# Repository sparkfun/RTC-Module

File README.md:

SparkFun DS1307 RTC Module
==================

[  
*DS1307 Real Time Clock Module (BOB-12708)*](https://www.sparkfun.com/products/12708)

The Real Time Clock (RTC) module uses the DS1307 to keep track of the current year, month, day as well as the current time.

Repository Contents
-------------------
* **/Hardware** - All Eagle design files (.brd, .sch). These go way back in time (before github was around) so be sure to dig back to the original commit to see the early versions of the Eagle files.
* **/Production** - Various test jigs and large panel layouts used for production.

Documentation
--------------
* **[Installing an Arduino Library Guide](https://learn.sparkfun.com/tutorials/installing-an-arduino-library)** - Basic information on how to install an Arduino library.
* **[Library](https://github.com/sparkfun/SparkFun_DS1307_RTC_Arduino_Library)** - Arduino library for the SparkFun DS1307 RTC Module.
* **[Hookup Guide](https://learn.sparkfun.com/tutorials/real-time-clock-module-hookup-guide)** - Basic hookup guide for the SparkFun DS1307 RTC Module.

Version History
---------------
* [v1.3](https://www.sparkfun.com/products/retired/99) Version 1.3

License Information
-------------------

The hardware is released under [Creative Commons ShareAlike 4.0 International](https://creativecommons.org/licenses/by-sa/4.0/).
The code is beerware; if you see me (or any other SparkFun employee) at the local, and you've found our code helpful, please buy us a round!

Distributed as-is; no warranty is given.

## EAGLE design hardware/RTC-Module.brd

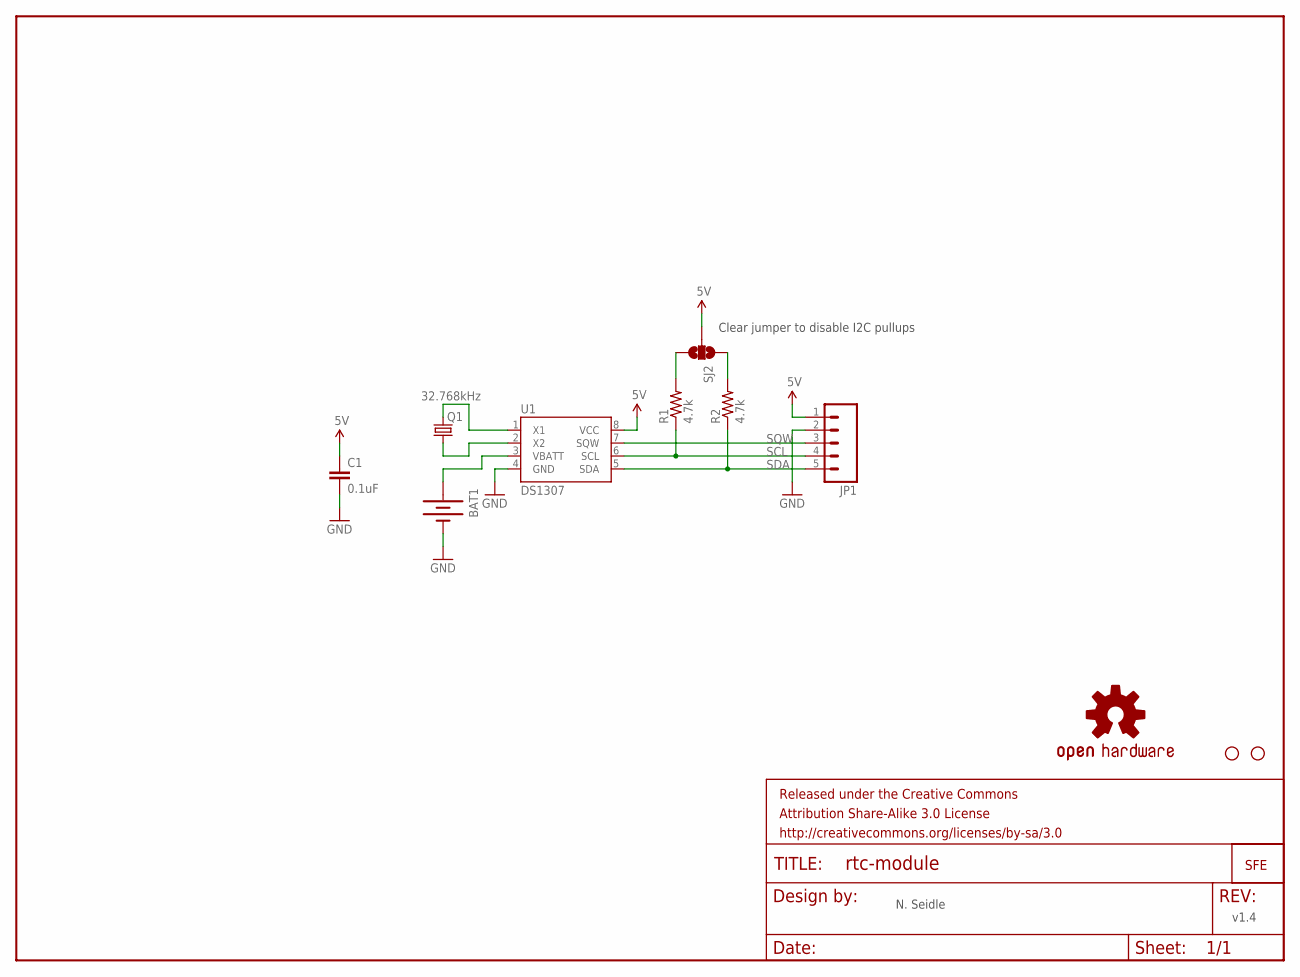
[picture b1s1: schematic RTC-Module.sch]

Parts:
BAT1: BATTERY12PTH; BATTCON_12MM_PTH
C1: 0.1uF; 0603-CAP
FRAME2: FRAME-LETTER; CREATIVE_COMMONS
JP1: M05PTH; 1X05
LOGO1: OSHW-LOGOS; OSHW-LOGO-S
Q1: 32.768kHz; CRYSTAL-32KHZ-SMD
R1, R2: 4.7k; 0603
SJ2: SOLDERJUMPER_2WAYPASTE1&2&3; SJ_3_PASTE1&2&3
U1: DS1307; SO08-TIGHT
U$1: LOGO-SFESK; SFE-LOGO-FLAME
U$6, U$7: STAND-OFF

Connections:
5V: C1.1, JP1.1, SJ2.2, U1.8 (VCC)
GND: BAT1.GND (-), C1.2, JP1.2, U1.4 (GND)
unnamed: Q1.X2 (2), U1.1 (X1)
unnamed: Q1.X1 (1), U1.2 (X2)
unnamed: BAT1.VCC@1 (+), U1.3 (VBATT)
unnamed: R1.2, SJ2.3
unnamed: R2.2, SJ2.1
SCL: JP1.4, R1.1, U1.6 (SCL)
SDA: JP1.5, R2.1, U1.5 (SDA)
SQW: JP1.3, U1.7 (SQW)

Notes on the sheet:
v1.4
N. Seidle
Clear jumper to disable I2C pullups

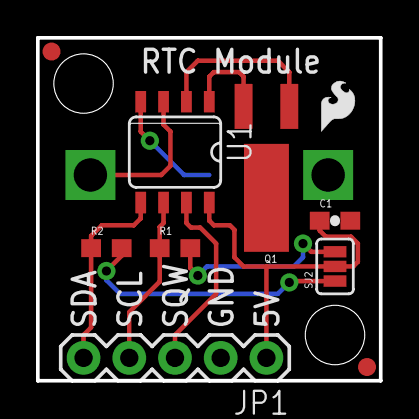
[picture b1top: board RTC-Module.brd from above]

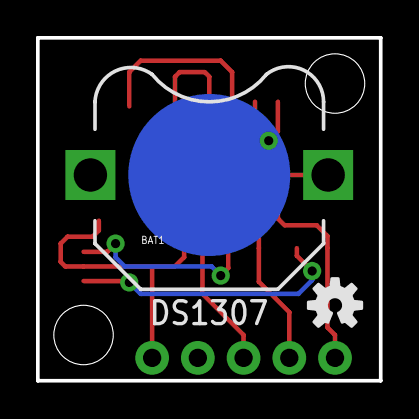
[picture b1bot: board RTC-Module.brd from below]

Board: 2 copper layers, 19.1 x 19.1 mm, 15 parts (2 on the bottom side), 10 nets.

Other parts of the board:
E$1, E$2: FIDUCIAL-1X2

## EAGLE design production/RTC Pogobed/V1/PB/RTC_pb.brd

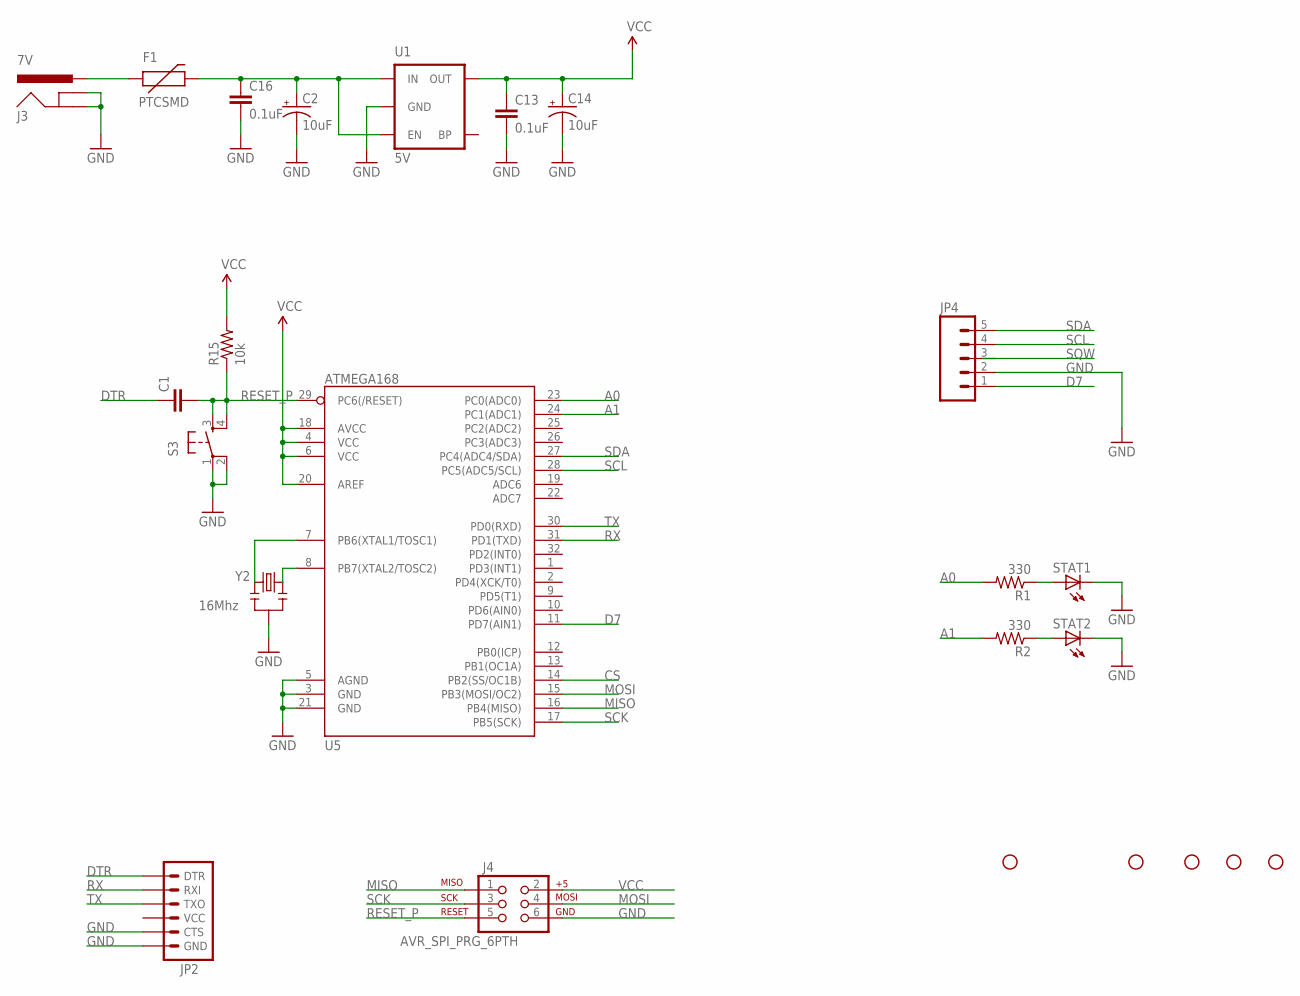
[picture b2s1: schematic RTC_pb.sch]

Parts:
C1: CAP0603-CAP; 0603-CAP
C2, C14: 10uF; EIA3216
C13, C16: 0.1uF; 0603-CAP
F1: PTCSMD; PTC-1206
J3: 7V; POWER_JACK_PTH_LOCK
J4: AVR_SPI_PRG_6PTH; 2X3
JP1, JP7, JP8, JP9, JP10: STAND-OFFTIGHT; STAND-OFF-TIGHT
JP2: ARDUINO_SERIAL_PROGRAMPTH; 1X06
JP4: M05PTH_LONGPADS; 1X05_LONGPADS
R1, R2: 330; 0603-RES
R15: 10k; 0603-RES
S3: TAC_SWITCHPTH; TACTILE-PTH
STAT1, STAT2: Yellow; LED-1206
U1: 3.3V; SOT23-5
U5: ATMEGA168; TQFP32-08
Y2: 8MHz; RESONATOR-SMD

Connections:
A0: R1.2, U5.23 (PC0(ADC0))
A1: R2.2, U5.24 (PC1(ADC1))
CS: U5.14 (PB2(SS/OC1B))
D7: JP4.1, U5.11 (PD7(AIN1))
DTR: C1.1, JP2.1 (DTR)
GND: C2.C (-), C13.2, C14.C (-), C16.2, J3.GND, J3.GNDBREAK, J4.6, JP2.5 (CTS), JP2.6 (GND), JP4.2, S3.1, S3.2, STAT1.C, STAT2.C, U1.2 (GND), U5.3 (GND), U5.5 (AGND), U5.21 (GND), Y2.2
MISO: J4.1, U5.16 (PB4(MISO))
MOSI: J4.4, U5.15 (PB3(MOSI/OC2))
unnamed: R1.1, STAT1.A
unnamed: R2.1, STAT2.A
unnamed: C2.A (+), C16.1, F1.2, U1.1 (IN), U1.3 (EN)
unnamed: U5.8 (PB7(XTAL2/TOSC2)), Y2.3
unnamed: U5.7 (PB6(XTAL1/TOSC1)), Y2.1
RAW: F1.1, J3.PWR
RESET_P: C1.2, J4.5, R15.1, S3.3, S3.4, U5.29 (PC6(/RESET))
RX: JP2.2 (RXI), U5.31 (PD1(TXD))
SCK: J4.3, U5.17 (PB5(SCK))
SCL: JP4.4, U5.28 (PC5(ADC5/SCL))
SDA: JP4.5, U5.27 (PC4(ADC4/SDA))
TX: JP2.3 (TXO), U5.30 (PD0(RXD))
VCC: C13.1, C14.A (+), J4.2, R15.2, U1.5 (OUT), U5.4 (VCC), U5.6 (VCC), U5.18 (AVCC), U5.20 (AREF)

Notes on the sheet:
16Mhz

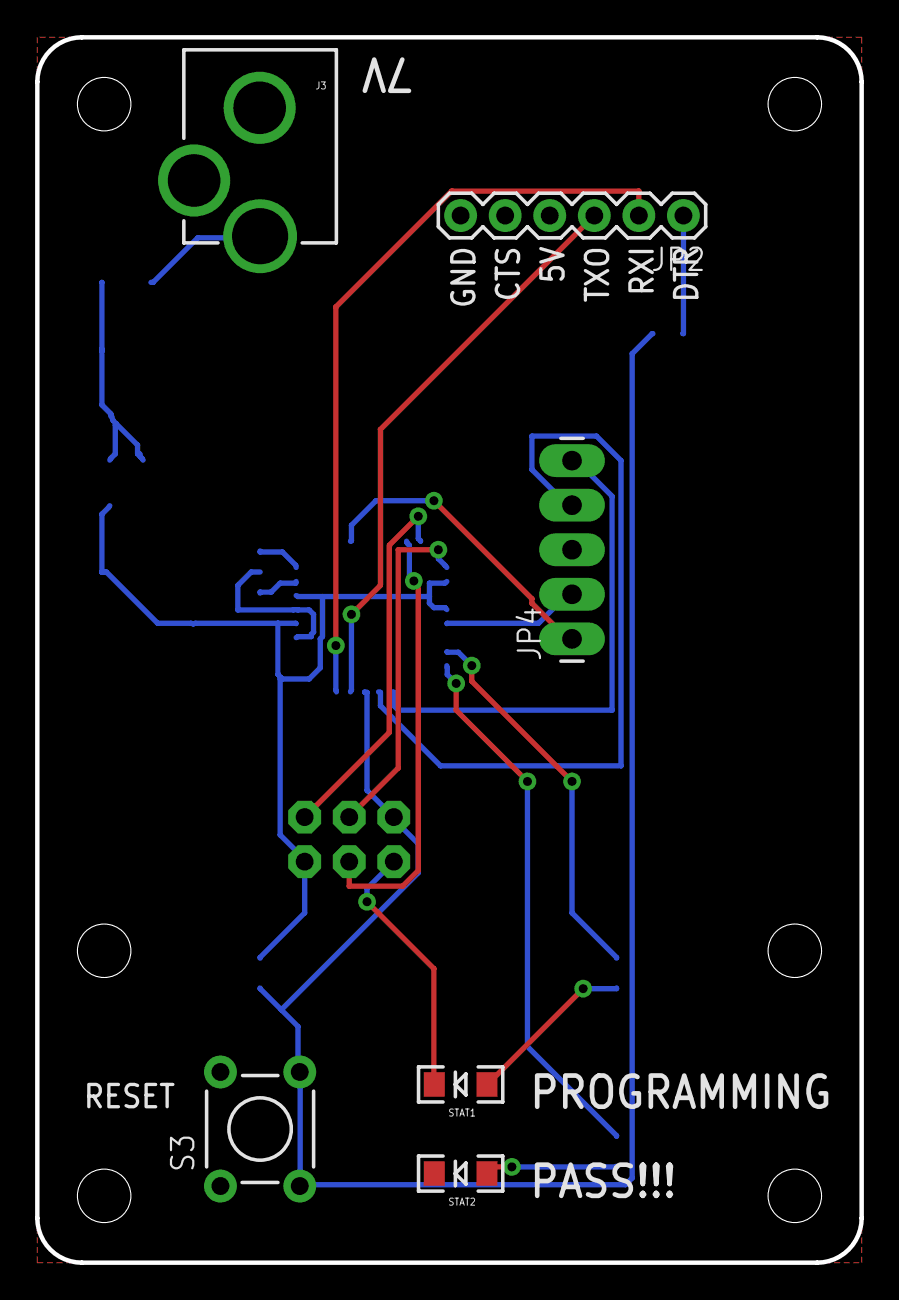
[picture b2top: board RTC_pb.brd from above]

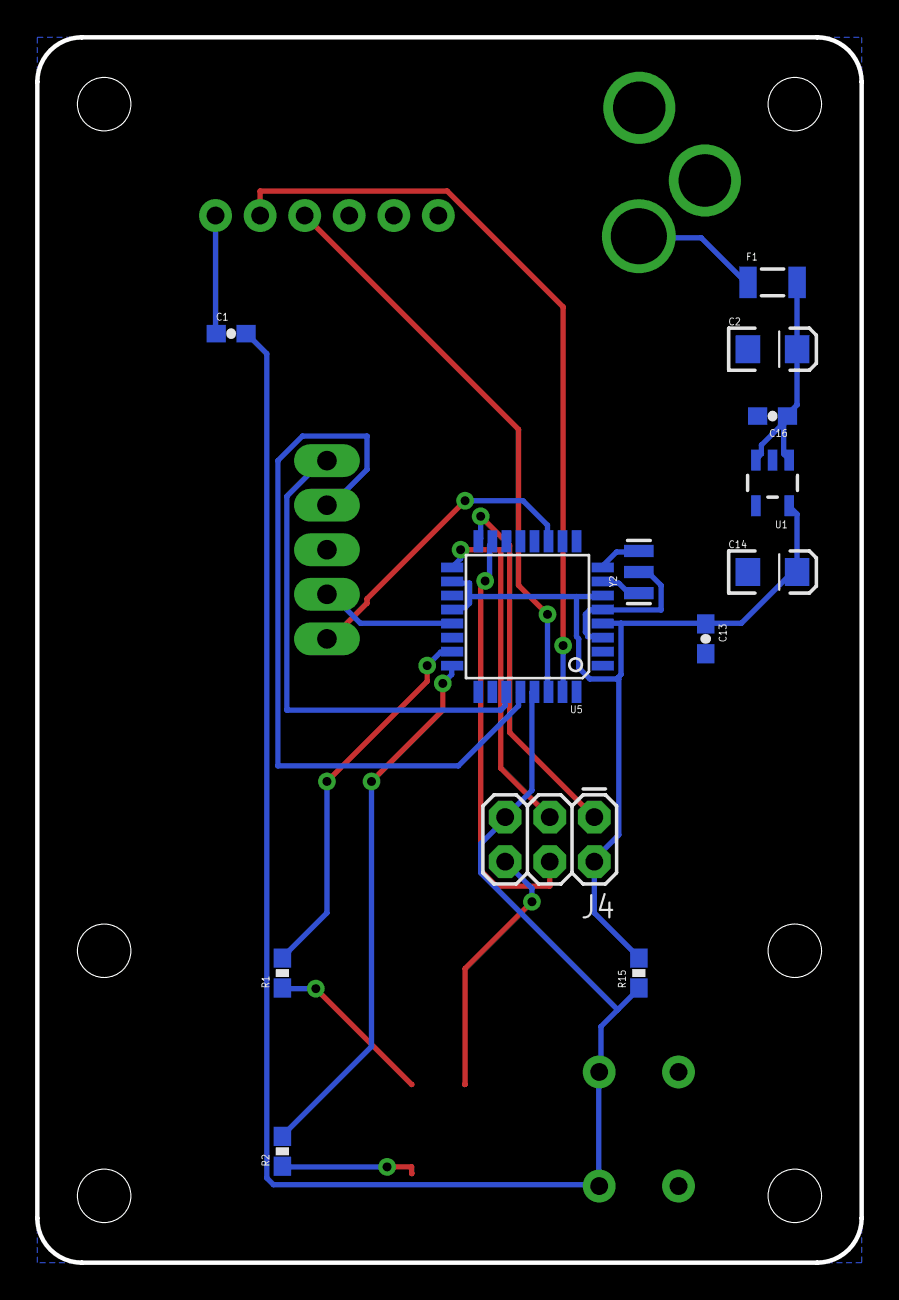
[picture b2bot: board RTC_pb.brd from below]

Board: 2 copper layers, 47.0 x 69.8 mm, 25 parts (13 on the bottom side), 20 nets.

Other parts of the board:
JP3: STAND-OFFTIGHT; STAND-OFF-TIGHT

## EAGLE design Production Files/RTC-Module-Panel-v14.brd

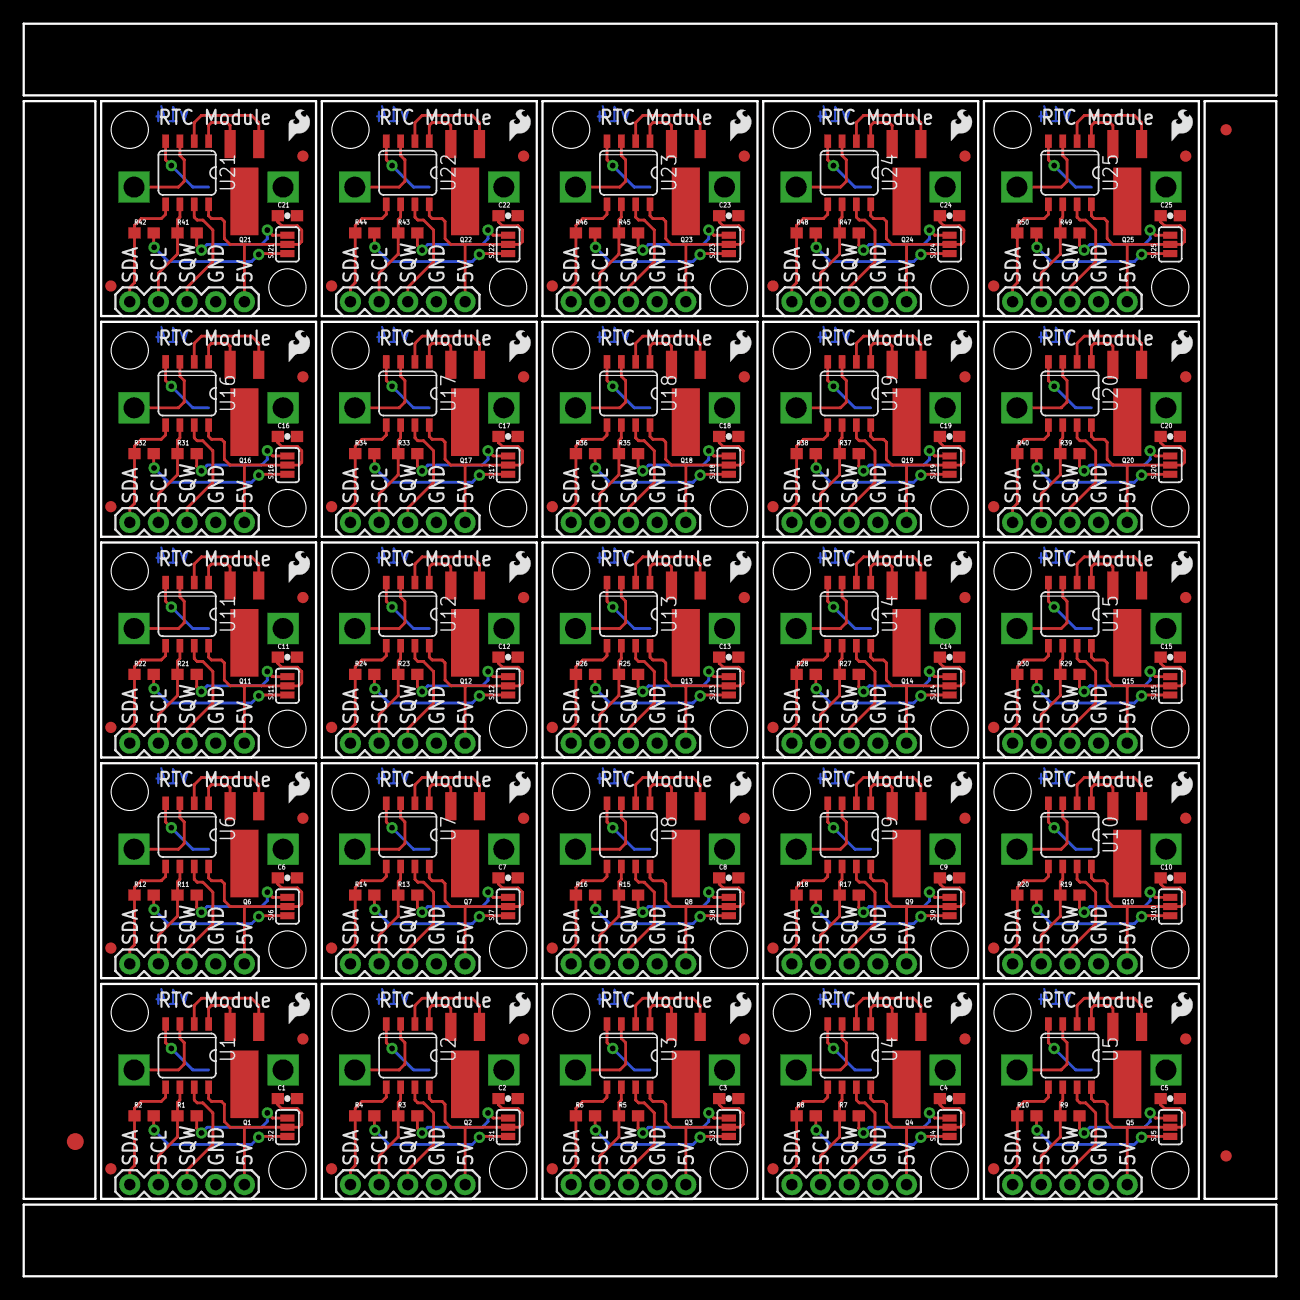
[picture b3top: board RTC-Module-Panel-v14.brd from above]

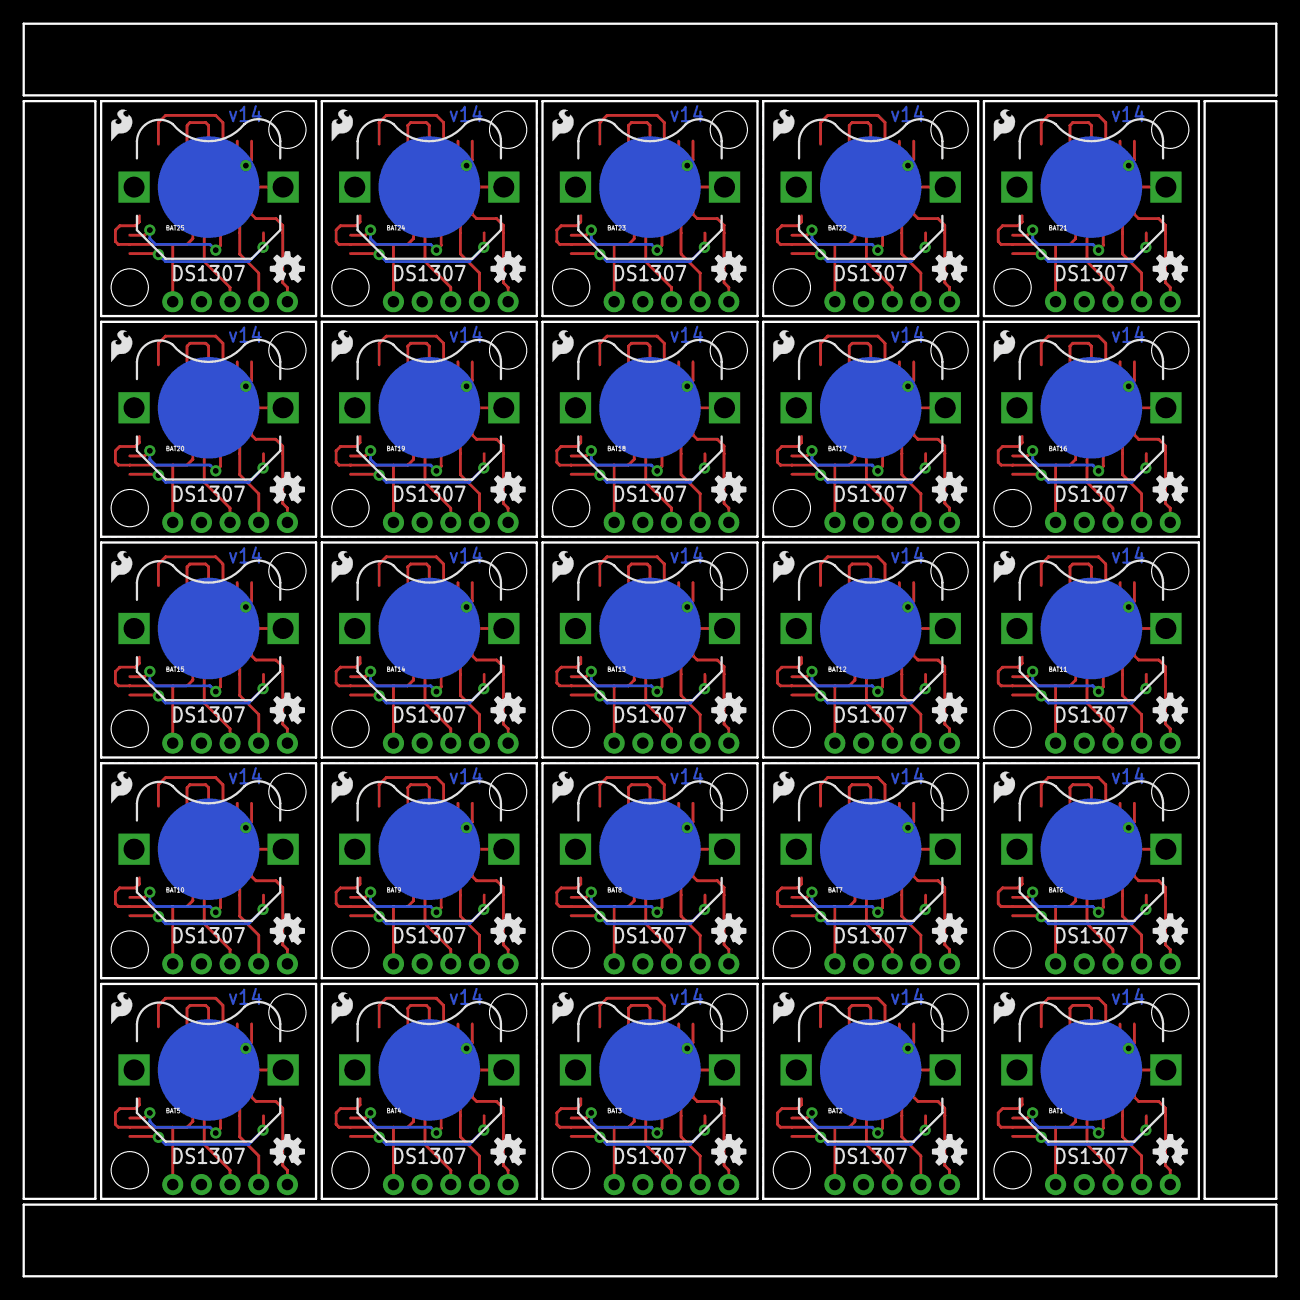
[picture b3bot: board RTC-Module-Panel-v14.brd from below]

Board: 2 copper layers, 111.0 x 111.0 mm, 378 parts (75 on the bottom side), 250 nets.

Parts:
BAT1, BAT2, BAT3, BAT4, BAT5, BAT6, BAT7, BAT8, BAT9, BAT10, BAT11, BAT12, BAT13, BAT14, BAT15, BAT16, BAT17, BAT18, BAT19, BAT20, BAT21, BAT22, BAT23, BAT24, BAT25: BATTCON_12MM_PTH
C1, C2, C3, C4, C5, C6, C7, C8, C9, C10, C11, C12, C13, C14, C15, C16, C17, C18, C19, C20, C21, C22, C23, C24, C25: 0.1uF; 0603-CAP
E$1, E$2, E$3, E$4, E$5, E$6, E$7, E$8, E$9, E$10, E$11, E$12, E$13, E$14, E$15, E$16, E$17, E$18, E$19, E$20, E$21, E$22, E$23, E$24, E$25, E$26, E$27, E$28, E$29, E$30, E$31, E$32, E$33, E$34, E$35, E$36, E$37, E$38, E$39, E$40, E$41, E$42, E$43, E$44, E$45, E$46, E$47, E$48, E$49, E$50, E$54, E$55: FIDUCIAL-1X2
E$51: FIDUCIAL-1.5X3
JP1, JP2, JP3, JP4, JP5, JP6, JP7, JP8, JP9, JP10, JP11, JP12, JP13, JP14, JP15, JP16, JP17, JP18, JP19, JP20, JP21, JP22, JP23, JP24, JP25: 1X05
LOGO1, LOGO2, LOGO3, LOGO4, LOGO5, LOGO6, LOGO7, LOGO8, LOGO9, LOGO10, LOGO11, LOGO12, LOGO13, LOGO14, LOGO15, LOGO16, LOGO17, LOGO18, LOGO19, LOGO20, LOGO21, LOGO22, LOGO23, LOGO24, LOGO25: OSHW-LOGOS; OSHW-LOGO-S
Q1, Q2, Q3, Q4, Q5, Q6, Q7, Q8, Q9, Q10, Q11, Q12, Q13, Q14, Q15, Q16, Q17, Q18, Q19, Q20, Q21, Q22, Q23, Q24, Q25: 32.768kHz; CRYSTAL-32KHZ-SMD
R1, R2, R3, R4, R5, R6, R7, R8, R9, R10, R11, R12, R13, R14, R15, R16, R17, R18, R19, R20, R21, R22, R23, R24, R25, R26, R27, R28, R29, R30, R31, R32, R33, R34, R35, R36, R37, R38, R39, R40, R41, R42, R43, R44, R45, R46, R47, R48, R49, R50: 4.7k; 0603
SJ1, SJ2, SJ3, SJ4, SJ5, SJ6, SJ7, SJ8, SJ9, SJ10, SJ11, SJ12, SJ13, SJ14, SJ15, SJ16, SJ17, SJ18, SJ19, SJ20, SJ21, SJ22, SJ23, SJ24, SJ25: SJ_3_PASTE1&2&3
U1, U2, U3, U4, U5, U6, U7, U8, U9, U10, U11, U12, U13, U14, U15, U16, U17, U18, U19, U20, U21, U22, U23, U24, U25: DS1307; SO08-TIGHT
U$1, U$2, U$3, U$8, U$9, U$12, U$13, U$16, U$17, U$20, U$21, U$24, U$25, U$28, U$29, U$32, U$33, U$36, U$37, U$40, U$41, U$44, U$45, U$48, U$49, U$52, U$53, U$56, U$57, U$60, U$61, U$64, U$65, U$68, U$69, U$72, U$73, U$76, U$77, U$80, U$81, U$84, U$85, U$88, U$89, U$92, U$93, U$96, U$97, U$100: LOGO-SFESK; SFE-LOGO-FLAME
U$4, U$5, U$6, U$7, U$10, U$11, U$14, U$15, U$18, U$19, U$22, U$23, U$26, U$27, U$30, U$31, U$34, U$35, U$38, U$39, U$42, U$43, U$46, U$47, U$50, U$51, U$54, U$55, U$58, U$59, U$62, U$63, U$66, U$67, U$70, U$71, U$74, U$75, U$78, U$79, U$82, U$83, U$86, U$87, U$90, U$91, U$94, U$95, U$98, U$99: STAND-OFF

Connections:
5V: C1.1, JP1.1, SJ2.2, U1.8
5V1: C2.1, JP2.1, SJ1.2, U2.8
5V2: C3.1, JP3.1, SJ3.2, U3.8
5V3: C4.1, JP4.1, SJ4.2, U4.8
5V4: C5.1, JP5.1, SJ5.2, U5.8
5V5: C6.1, JP6.1, SJ6.2, U6.8
5V6: C7.1, JP7.1, SJ7.2, U7.8
5V7: C8.1, JP8.1, SJ8.2, U8.8
5V8: C9.1, JP9.1, SJ9.2, U9.8
5V9: C10.1, JP10.1, SJ10.2, U10.8
5V10: C11.1, JP11.1, SJ11.2, U11.8
5V11: C12.1, JP12.1, SJ12.2, U12.8
5V12: C13.1, JP13.1, SJ13.2, U13.8
5V13: C14.1, JP14.1, SJ14.2, U14.8
5V14: C15.1, JP15.1, SJ15.2, U15.8
5V15: C16.1, JP16.1, SJ16.2, U16.8
5V16: C17.1, JP17.1, SJ17.2, U17.8
5V17: C18.1, JP18.1, SJ18.2, U18.8
5V18: C19.1, JP19.1, SJ19.2, U19.8
5V19: C20.1, JP20.1, SJ20.2, U20.8
5V20: C21.1, JP21.1, SJ21.2, U21.8
5V21: C22.1, JP22.1, SJ22.2, U22.8
5V22: C23.1, JP23.1, SJ23.2, U23.8
5V23: C24.1, JP24.1, SJ24.2, U24.8
5V24: C25.1, JP25.1, SJ25.2, U25.8
GND: BAT1.GND, C1.2, JP1.2, U1.4
GND1: BAT2.GND, C2.2, JP2.2, U2.4
GND2: BAT3.GND, C3.2, JP3.2, U3.4
GND3: BAT4.GND, C4.2, JP4.2, U4.4
GND4: BAT5.GND, C5.2, JP5.2, U5.4
GND5: BAT6.GND, C6.2, JP6.2, U6.4
GND6: BAT7.GND, C7.2, JP7.2, U7.4
GND7: BAT8.GND, C8.2, JP8.2, U8.4
GND8: BAT9.GND, C9.2, JP9.2, U9.4
GND9: BAT10.GND, C10.2, JP10.2, U10.4
GND10: BAT11.GND, C11.2, JP11.2, U11.4
GND11: BAT12.GND, C12.2, JP12.2, U12.4
GND12: BAT13.GND, C13.2, JP13.2, U13.4
GND13: BAT14.GND, C14.2, JP14.2, U14.4
GND14: BAT15.GND, C15.2, JP15.2, U15.4
GND15: BAT16.GND, C16.2, JP16.2, U16.4
GND16: BAT17.GND, C17.2, JP17.2, U17.4
GND17: BAT18.GND, C18.2, JP18.2, U18.4
GND18: BAT19.GND, C19.2, JP19.2, U19.4
GND19: BAT20.GND, C20.2, JP20.2, U20.4
GND20: BAT21.GND, C21.2, JP21.2, U21.4
GND21: BAT22.GND, C22.2, JP22.2, U22.4
GND22: BAT23.GND, C23.2, JP23.2, U23.4
GND23: BAT24.GND, C24.2, JP24.2, U24.4
GND24: BAT25.GND, C25.2, JP25.2, U25.4
unnamed: Q1.X2, U1.1
unnamed: Q1.X1, U1.2
unnamed: Q2.X2, U2.1
unnamed: BAT1.VCC@1, U1.3
unnamed: R1.2, SJ2.3
unnamed: R2.2, SJ2.1
unnamed: Q2.X1, U2.2
unnamed: BAT2.VCC@1, U2.3
unnamed: R3.2, SJ1.3
unnamed: R4.2, SJ1.1
unnamed: Q3.X2, U3.1
unnamed: Q3.X1, U3.2
unnamed: BAT3.VCC@1, U3.3
unnamed: R5.2, SJ3.3
unnamed: R6.2, SJ3.1
unnamed: Q4.X2, U4.1
unnamed: Q4.X1, U4.2
unnamed: BAT4.VCC@1, U4.3
unnamed: R7.2, SJ4.3
unnamed: R8.2, SJ4.1
unnamed: Q5.X2, U5.1
unnamed: Q5.X1, U5.2
unnamed: BAT5.VCC@1, U5.3
unnamed: R9.2, SJ5.3
unnamed: R10.2, SJ5.1
unnamed: Q6.X2, U6.1
unnamed: Q6.X1, U6.2
unnamed: BAT6.VCC@1, U6.3
unnamed: R11.2, SJ6.3
unnamed: R12.2, SJ6.1
unnamed: Q7.X2, U7.1
unnamed: Q7.X1, U7.2
unnamed: BAT7.VCC@1, U7.3
unnamed: R13.2, SJ7.3
unnamed: R14.2, SJ7.1
unnamed: Q8.X2, U8.1
unnamed: Q8.X1, U8.2
unnamed: BAT8.VCC@1, U8.3
unnamed: R15.2, SJ8.3
unnamed: R16.2, SJ8.1
unnamed: Q9.X2, U9.1
unnamed: Q9.X1, U9.2
unnamed: BAT9.VCC@1, U9.3
unnamed: R17.2, SJ9.3
unnamed: R18.2, SJ9.1
unnamed: Q10.X2, U10.1
unnamed: Q10.X1, U10.2
unnamed: BAT10.VCC@1, U10.3
unnamed: R19.2, SJ10.3
unnamed: R20.2, SJ10.1
unnamed: Q11.X2, U11.1
unnamed: Q11.X1, U11.2
unnamed: BAT11.VCC@1, U11.3
unnamed: R21.2, SJ11.3
unnamed: R22.2, SJ11.1
unnamed: Q12.X2, U12.1
unnamed: Q12.X1, U12.2
unnamed: BAT12.VCC@1, U12.3
unnamed: R23.2, SJ12.3
unnamed: R24.2, SJ12.1
unnamed: Q13.X2, U13.1
unnamed: Q13.X1, U13.2
unnamed: BAT13.VCC@1, U13.3
unnamed: R25.2, SJ13.3
unnamed: R26.2, SJ13.1
unnamed: Q14.X2, U14.1
unnamed: Q14.X1, U14.2
unnamed: BAT14.VCC@1, U14.3
unnamed: R27.2, SJ14.3
unnamed: R28.2, SJ14.1
unnamed: Q15.X2, U15.1
unnamed: Q15.X1, U15.2
unnamed: BAT15.VCC@1, U15.3
unnamed: R29.2, SJ15.3
unnamed: R30.2, SJ15.1
unnamed: Q16.X2, U16.1
unnamed: Q16.X1, U16.2
unnamed: BAT16.VCC@1, U16.3
unnamed: R31.2, SJ16.3
unnamed: R32.2, SJ16.1
unnamed: Q17.X2, U17.1
unnamed: Q17.X1, U17.2
unnamed: BAT17.VCC@1, U17.3
unnamed: R33.2, SJ17.3
unnamed: R34.2, SJ17.1
unnamed: Q18.X2, U18.1
unnamed: Q18.X1, U18.2
unnamed: BAT18.VCC@1, U18.3
unnamed: R35.2, SJ18.3
unnamed: R36.2, SJ18.1
unnamed: Q19.X2, U19.1
unnamed: Q19.X1, U19.2
unnamed: BAT19.VCC@1, U19.3
unnamed: R37.2, SJ19.3
unnamed: R38.2, SJ19.1
unnamed: Q20.X2, U20.1
unnamed: Q20.X1, U20.2
unnamed: BAT20.VCC@1, U20.3
unnamed: R39.2, SJ20.3
unnamed: R40.2, SJ20.1
unnamed: Q21.X2, U21.1
unnamed: Q21.X1, U21.2
unnamed: BAT21.VCC@1, U21.3
unnamed: R41.2, SJ21.3
unnamed: R42.2, SJ21.1
unnamed: Q22.X2, U22.1
unnamed: Q22.X1, U22.2
unnamed: BAT22.VCC@1, U22.3
unnamed: R43.2, SJ22.3
unnamed: R44.2, SJ22.1
unnamed: Q23.X2, U23.1
unnamed: Q23.X1, U23.2
unnamed: BAT23.VCC@1, U23.3
unnamed: R45.2, SJ23.3
unnamed: R46.2, SJ23.1
unnamed: Q24.X2, U24.1
unnamed: Q24.X1, U24.2
unnamed: BAT24.VCC@1, U24.3
unnamed: R47.2, SJ24.3
unnamed: R48.2, SJ24.1
unnamed: Q25.X2, U25.1
unnamed: Q25.X1, U25.2
unnamed: BAT25.VCC@1, U25.3
unnamed: R49.2, SJ25.3
unnamed: R50.2, SJ25.1
SCL: JP1.4, R1.1, U1.6
SCL1: JP2.4, R3.1, U2.6
SCL2: JP3.4, R5.1, U3.6
SCL3: JP4.4, R7.1, U4.6
SCL4: JP5.4, R9.1, U5.6
SCL5: JP6.4, R11.1, U6.6
SCL6: JP7.4, R13.1, U7.6
SCL7: JP8.4, R15.1, U8.6
SCL8: JP9.4, R17.1, U9.6
SCL9: JP10.4, R19.1, U10.6
SCL10: JP11.4, R21.1, U11.6
SCL11: JP12.4, R23.1, U12.6
SCL12: JP13.4, R25.1, U13.6
SCL13: JP14.4, R27.1, U14.6
SCL14: JP15.4, R29.1, U15.6
SCL15: JP16.4, R31.1, U16.6
SCL16: JP17.4, R33.1, U17.6
SCL17: JP18.4, R35.1, U18.6
SCL18: JP19.4, R37.1, U19.6
SCL19: JP20.4, R39.1, U20.6
SCL20: JP21.4, R41.1, U21.6
SCL21: JP22.4, R43.1, U22.6
SCL22: JP23.4, R45.1, U23.6
SCL23: JP24.4, R47.1, U24.6
SCL24: JP25.4, R49.1, U25.6
SDA: JP1.5, R2.1, U1.5
SDA1: JP2.5, R4.1, U2.5
SDA2: JP3.5, R6.1, U3.5
SDA3: JP4.5, R8.1, U4.5
SDA4: JP5.5, R10.1, U5.5
SDA5: JP6.5, R12.1, U6.5
SDA6: JP7.5, R14.1, U7.5
SDA7: JP8.5, R16.1, U8.5
SDA8: JP9.5, R18.1, U9.5
SDA9: JP10.5, R20.1, U10.5
SDA10: JP11.5, R22.1, U11.5
SDA11: JP12.5, R24.1, U12.5
SDA12: JP13.5, R26.1, U13.5
SDA13: JP14.5, R28.1, U14.5
SDA14: JP15.5, R30.1, U15.5
SDA15: JP16.5, R32.1, U16.5
SDA16: JP17.5, R34.1, U17.5
SDA17: JP18.5, R36.1, U18.5
SDA18: JP19.5, R38.1, U19.5
SDA19: JP20.5, R40.1, U20.5
SDA20: JP21.5, R42.1, U21.5
SDA21: JP22.5, R44.1, U22.5
SDA22: JP23.5, R46.1, U23.5
SDA23: JP24.5, R48.1, U24.5
SDA24: JP25.5, R50.1, U25.5
SQW: JP1.3, U1.7
SQW1: JP2.3, U2.7
SQW2: JP3.3, U3.7
SQW3: JP4.3, U4.7
SQW4: JP5.3, U5.7
SQW5: JP6.3, U6.7
SQW6: JP7.3, U7.7
SQW7: JP8.3, U8.7
SQW8: JP9.3, U9.7
SQW9: JP10.3, U10.7
SQW10: JP11.3, U11.7
SQW11: JP12.3, U12.7
SQW12: JP13.3, U13.7
SQW13: JP14.3, U14.7
SQW14: JP15.3, U15.7
SQW15: JP16.3, U16.7
SQW16: JP17.3, U17.7
SQW17: JP18.3, U18.7
SQW18: JP19.3, U19.7
SQW19: JP20.3, U20.7
SQW20: JP21.3, U21.7
SQW21: JP22.3, U22.7
SQW22: JP23.3, U23.7
SQW23: JP24.3, U24.7
SQW24: JP25.3, U25.7

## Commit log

2013-12-11 Initial commit. Contains original versions of hardware.
    This commit contains the early versions v1.0 to v1.3.
2013-12-12 Adding I2C resistors and increase center battery pad.
    Added 4.7ks. Made center pad on battery holder larger and round.
    Modified cream for center battery pad. Various clean up of schematic.
    Brought overall design up to current engineering rules.
2013-12-12 Removed old board files.
    Because that's what github is for.
2013-12-12 Routing and silk changes
    1.) Changed trace routes to go straight away from IC.
    2.) Changed all silk to vector
    3.) Made pin labels smaller to avoid interfering with resistors.
    3.) Standardized trace width to .01
    4.) Moved R1 to the left and rerouted SQW trace.
    5.) Added tRestrict under IC.
2013-12-12 Removed Sparkfun web logo
    Just not enough room for it. The SF flame should suffice.
2013-12-16 Fixed I2C jumper. Silk mods. Removed restrict polygon.
2013-12-16 Small changes to silk. Add prototype files.
2013-12-16 Removing gerber files.
2014-01-09 deleted old panels and pogobed files
2014-01-30 Minor fixes
    1.) added i2c address to sch
    2.) added rev number in bottom copper
    3.) updated revision info in sch and brd
    4.) moved fiducials to clear drc
    5.) cleaned up sda trace a bit
    6.) added flame to bottom silk
2014-01-30 created panel v14
2014-07-30 Updating README to new product links

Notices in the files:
parts and their libraries:
SparkFun-FreqCtrl: Licensing: CC v3.0 Share-Alike You are welcome to use this library for commercial purposes.
SparkFun-Aesthetics: Released under the Creative Commons Attribution Share-Alike 3.0 License
SparkFun-Aesthetics: http://creativecommons.org/licenses/by-sa/3.0
